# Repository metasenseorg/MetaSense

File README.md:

# MetaSense
MetaSense Project Repository of Data, Software, and Hardware.

Archival website: https://sites.google.com/a/eng.ucsd.edu/citisense/

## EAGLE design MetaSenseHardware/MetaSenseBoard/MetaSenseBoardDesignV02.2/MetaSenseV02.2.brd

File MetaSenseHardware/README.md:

# README #

[MetaSense Project](http://metasense.ucsd.edu)

# MetaSense Hardware #
This repository contains the hardware (electrical and mechanical enclosures) for the MetaSense Air Quality Sensing Platform.

## MetaSenseBoard ##
The electrical design for the MetaSense Air Quality Sensing Platform can be found here. A schematic can be found in each MetaSenseBoardDesign version folder along with gerbers that can be used for ordering and building PCBs.

If you want to modify or update the board files, the .brd and .sch files can be opened in Eagle.

### VOC Interface Board ###
The VOC interface board connects into the VOC and I2C Extension header (JP14). The board connects to two different VOC sensors:
* Mocon pID-TECH eVx: photoionization VOC sensor with 4-pin connection and analog output
* ams iAQ-core: MOS VOC sensor with I2C interface for TVOC equivalent measurement

## MetaSense Enclosure ##
The enclosures were developed in Autodesk Fusion. Both are meant to be used without the VOC interface board.

### Enclosure v1.3 ###
The standard enclosure for the MetaSense Air Quality Sensing Platform. The shell is split into top and bottom halves, which are connected by through bolts that both hold the board in place and secure the shell. Velcro straps can be run through the bottom to allow attachment to objects.

### Alternate Drone v1.3 ###
The alternate enclosure for the MetaSense Air Quality Sensing Platform allows the sensor to be connected directly to the bottom of a DJI F450 Quadcopter base.

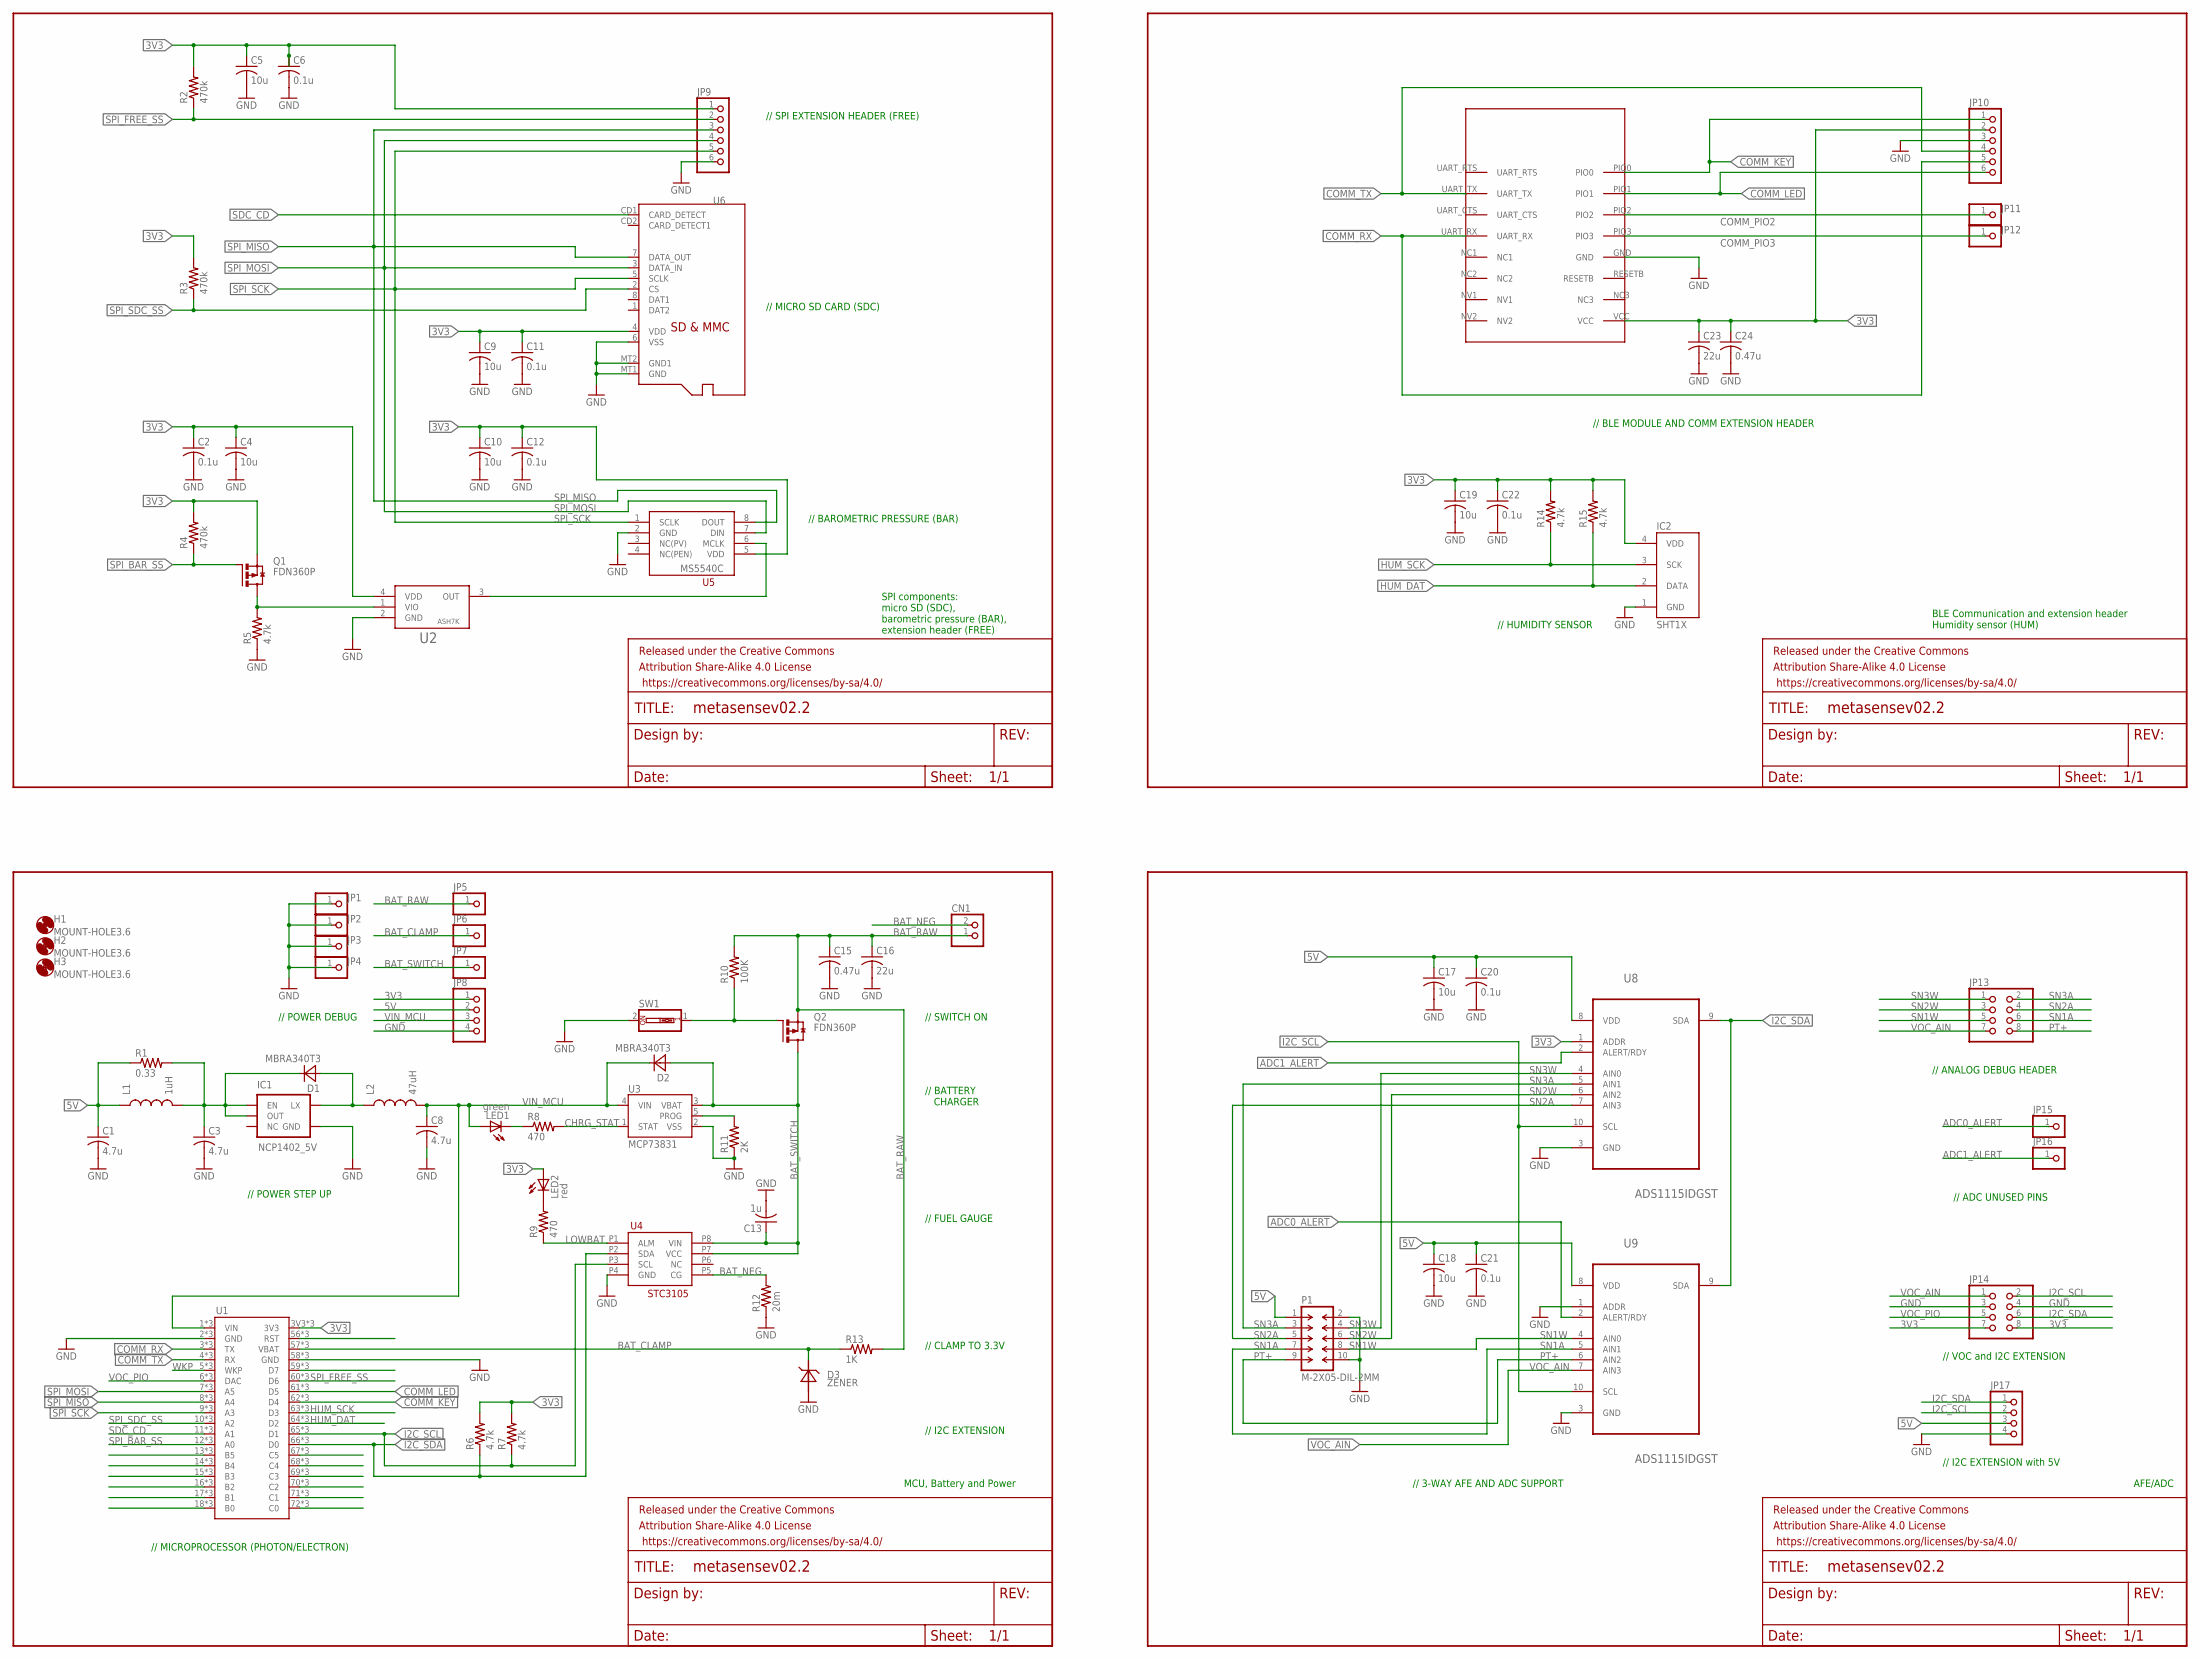
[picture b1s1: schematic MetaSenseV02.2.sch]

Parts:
C1, C3, C8: 4.7u; C0805; MPN IHLP2525CZER4R7M01
C2, C6, C11, C12, C20, C21, C22: 0.1u; C0805; MPN C0603C102J5GACTU
C4, C5, C9, C10, C17, C18, C19: 10u; C0805; MPN C0805C106Z8VACTU
C13: 1u; C0805; MPN C0402C471K5RACTU
C15, C24: 0.47u; C0805; MPN C0402C471K5RACTU
C16, C23: 22u; C0805
CN1: JST_2PIN-THM; JST-PH-2-THM
D1, D2: MBRA340T3; SMA
D3: ZENER; SOD-123_MINI-SMA
FRAME1, FRAME2, FRAME3, FRAME4: FRAME-LETTERNO_PACKAGE; DUMMY
H1, H2, H3: MOUNT-HOLE3.6; 3,6
IC1: NCP1402_5V; SOT23-5; MPN NCP1402SN50T1G
IC2: SHT1X; MPN SHT11
JP1, JP2, JP3, JP4, JP5, JP6, JP7, JP11, JP12, JP15, JP16: PINHD-1X1; 1X01
JP8, JP17: PINHD-1X4; 1X04
JP9, JP10: PINHD-1X6; 1X06
JP13, JP14: PINHD-2X4; 2X04
L1: 1uH; 0805; MPN LQM21NN1R0K10D
L2: 47uH; 0805
LED1: green; CHIPLED_0805; MPN NTE30003
LED2: red; CHIPLED_0805; MPN NTE30002
P1: M-2X05-DIL-2MM; DIL-2MM-2X05
Q1, Q2: FDN360P; SUPER-SOT3; MPN FDN360P
R1: 0.33; R0805
R2, R3, R4: 470k; R0805; MPN CRCW0805470KJNEA
R5, R6, R7, R14, R15: 4.7k; R0805; MPN CRCW08054K70JNEA
R8, R9: 470; R0805
R10: 100K; R0805; MPN ERA-6AEB104V
R11: 2K; R0805
R12: 20m; R0805
R13: 1K; R0805; MPN ERJ-6ENF1001V
SW1: SW_DIP-1; EDG-01
U1: ELECTRONDUALROW; ELECTRON_DUAL-ROW
U2: ASH7K-OSCILLATOR; SMD-4PAD
U3: MCP73831; SOT23-5; MPN MCP73831T-2DCI/OT
U4: STC3105; TDFN-8-3X2MM
U5: MS5540CSMD; SMD-HYBRID
U6: MICROSD; MPN 2908-05WB-MG
U7: HM-11
U8, U9: ADS1115IDGST; SOP50P490X110-10N

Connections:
3V3: C2.1, C4.1, C5.1, C6.1, C9.1, C10.1, C11.1, C12.1, C19.1, C22.1, C23.1, C24.1, IC2.4 (VDD), JP8.1, JP9.1, JP10.2, JP14.7, JP14.8, LED2.A, Q1.2 (S), R2.2, R3.2, R4.2, R6.2, R7.2, R14.2, R15.2, U1.3V3, U1.55 (3V3), U1.91 (3V3), U2.4 (VDD), U5.5 (VDD), U6.4 (VDD), U7.VCC, U8.1 (ADDR)
5V: C1.1, C17.1, C18.1, C20.1, C21.1, JP8.2, JP17.3, L1.1, P1.1, R1.1, U8.8 (VDD), U9.8 (VDD)
ADC0_ALERT: JP15.1, U9.2 (ALERT/RDY)
ADC1_ALERT: JP16.1, U8.2 (ALERT/RDY)
BAT_CLAMP: D3.C (CAT), JP6.1, R13.1, U1.57 (VBAT), U1.93 (VBAT), U1.VBAT
BAT_NEG: CN1.2 (1), R12.2, U4.P5 (CG)
BAT_RAW: C15.1, C16.1, CN1.1 (2), JP5.1, Q2.2 (S), R10.2, R13.2
BAT_SWITCH: C13.1, D2.A, JP7.1, Q2.3 (D), U3.3 (VBAT), U4.P7 (VCC), U4.P8 (VIN)
CHRG_STAT: R8.2, U3.1 (STAT)
COMM_KEY: JP10.1, U1.62 (D4), U1.98 (D4), U1.D4, U7.PIO0
COMM_LED: JP10.6, U1.61 (D5), U1.97 (D5), U1.D5, U7.PIO1
COMM_PIO2: JP11.1, U7.PIO2
COMM_PIO3: JP12.1, U7.PIO3
COMM_RX: JP10.5, U1.3 (TX), U1.39 (TX), U1.TX, U7.UART_RX
COMM_TX: JP10.4, U1.4 (RX), U1.40 (RX), U1.RX, U7.UART_TX
GND: C1.2, C2.2, C3.2, C4.2, C5.2, C6.2, C8.2, C9.2, C10.2, C11.2, C12.2, C13.2, C15.2, C16.2, C17.2, C18.2, C19.2, C20.2, C21.2, C22.2, C23.2, C24.2, D3.A (AN), IC1.4 (GND), IC2.1 (GND), JP1.1, JP2.1, JP3.1, JP4.1, JP8.4, JP9.6, JP10.3, JP14.3, JP14.4, JP17.4, P1.2, P1.10, R5.1, R11.1, R12.1, SW1.2, U1.2 (GND), U1.38 (GND), U1.58 (GND), U1.94 (GND), U1.GND, U1.GND@2 (GND), U2.2 (GND), U3.2 (VSS), U4.P4 (GND), U5.2 (GND), U6.6 (VSS), U6.MT1 (GND), U6.MT2 (GND1), U7.GND, U8.3 (GND), U9.1 (ADDR), U9.3 (GND)
HUM_DAT: IC2.2 (DATA), R15.1, U1.64 (D2), U1.100 (D2), U1.D2
HUM_SCK: IC2.3 (SCK), R14.1, U1.63 (D3), U1.99 (D3), U1.D3
I2C_SCL: JP14.2, JP17.2, R7.1, U1.65 (D1), U1.101 (D1), U1.D1, U4.P3 (SCL), U8.10 (SCL), U9.10 (SCL)
I2C_SDA: JP14.6, JP17.1, R6.1, U1.66 (D0), U1.102 (D0), U1.D0, U4.P2 (SDA), U8.9 (SDA), U9.9 (SDA)
LOWBAT: R9.1, U4.P1 (ALM)
unnamed: Q1.3 (D), R5.2, U2.1 (VIO)
unnamed: C3.1, D1.C, IC1.1 (EN), IC1.2 (OUT), L1.2, R1.2
unnamed: LED2.C, R9.2
unnamed: D1.A, IC1.5 (LX), L2.1
unnamed: U1.56 (RST), U1.92 (RST), U1.RST
unnamed: U1.67 (C5), U1.103 (C5), U1.C5
unnamed: R11.2, U3.5 (PROG)
unnamed: LED1.C, R8.1
unnamed: Q2.1 (G), R10.1, SW1.1
unnamed: U1.68 (C4), U1.104 (C4), U1.C4
unnamed: U2.3 (OUT), U5.6 (MCLK)
unnamed: U1.69 (C3), U1.105 (C3), U1.C3
unnamed: U1.70 (C2), U1.106 (C2), U1.C2
unnamed: U1.71 (C1), U1.107 (C1), U1.C1
unnamed: U1.72 (C0), U1.108 (C0), U1.C0
unnamed: U1.13 (B5), U1.49 (B5), U1.B5
unnamed: U1.59 (D7), U1.95 (D7), U1.D7
unnamed: U1.14 (B4), U1.50 (B4), U1.B4
unnamed: U1.15 (B3), U1.51 (B3), U1.B3
unnamed: U1.16 (B2), U1.52 (B2), U1.B2
unnamed: U1.17 (B1), U1.53 (B1), U1.B1
unnamed: U1.18 (B0), U1.54 (B0), U1.B0
PT+: JP13.8, P1.9, U9.6 (AIN2)
SDC_CD: U1.11 (A1), U1.47 (A1), U1.A1, U6.CD1 (CARD_DETECT)
SN1A: JP13.6, P1.7, U9.5 (AIN1)
SN1W: JP13.5, P1.8, U9.4 (AIN0)
SN2A: JP13.4, P1.5, U8.7 (AIN3)
SN2W: JP13.3, P1.6, U8.6 (AIN2)
SN3A: JP13.2, P1.3, U8.5 (AIN1)
SN3W: JP13.1, P1.4, U8.4 (AIN0)
SPI_BAR_SS: Q1.1 (G), R4.1, U1.12 (A0), U1.48 (A0), U1.A0
SPI_FREE_SS: JP9.2, R2.1, U1.60 (D6), U1.96 (D6), U1.D6
SPI_MISO: JP9.3, U1.8 (A4), U1.44 (A4), U1.A4, U5.8 (DOUT), U6.7 (DATA_OUT)
SPI_MOSI: JP9.4, U1.7 (A5), U1.43 (A5), U1.A5, U5.7 (DIN), U6.3 (DATA_IN)
SPI_SCK: JP9.5, U1.9 (A3), U1.45 (A3), U1.A3, U5.1 (SCLK), U6.5 (SCLK)
SPI_SDC_SS: R3.1, U1.10 (A2), U1.46 (A2), U1.A2, U6.2 (CS)
VIN_MCU: C8.1, D2.C, JP8.3, L2.2, LED1.A, U1.1 (VIN), U1.37 (VIN), U1.VIN, U3.4 (VIN)
VOC_AIN: JP13.7, JP14.1, U9.7 (AIN3)
VOC_PIO: JP14.5, U1.6 (DAC), U1.42 (DAC), U1.DAC
WKP: U1.5 (WKP), U1.41 (WKP), U1.WKP

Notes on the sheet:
MCU, Battery and Power
AFE/ADC
SPI components: micro SD (SDC), barometric pressure (BAR), extension header (FREE)
// BATTERY CHARGER
// FUEL GAUGE
// SWITCH ON
// POWER STEP UP
// 3-WAY AFE AND ADC SUPPORT
// BLE MODULE AND COMM EXTENSION HEADER
// HUMIDITY SENSOR
// SPI EXTENSION HEADER (FREE)
// MICRO SD CARD (SDC)
// BAROMETRIC PRESSURE (BAR)
BLE Communication and extension header Humidity sensor (HUM)
// ANALOG DEBUG HEADER
// MICROPROCESSOR (PHOTON/ELECTRON)
// I2C EXTENSION
// POWER DEBUG
// CLAMP TO 3.3V
// ADC UNUSED PINS
// VOC and I2C EXTENSION
// I2C EXTENSION with 5V

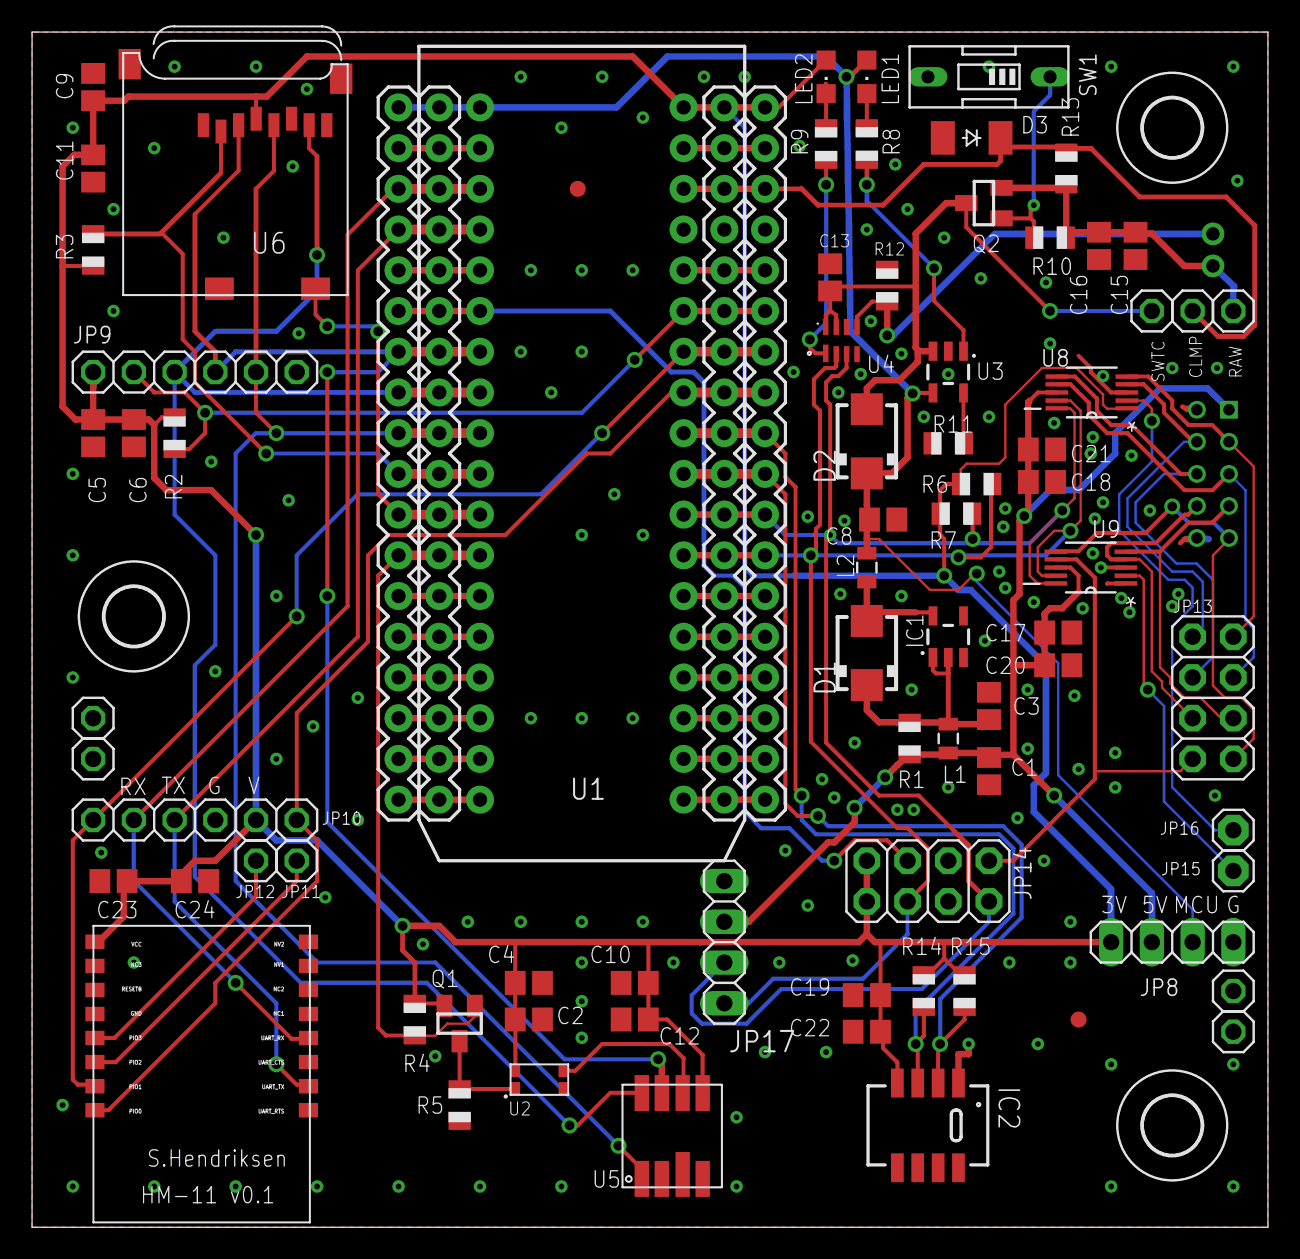
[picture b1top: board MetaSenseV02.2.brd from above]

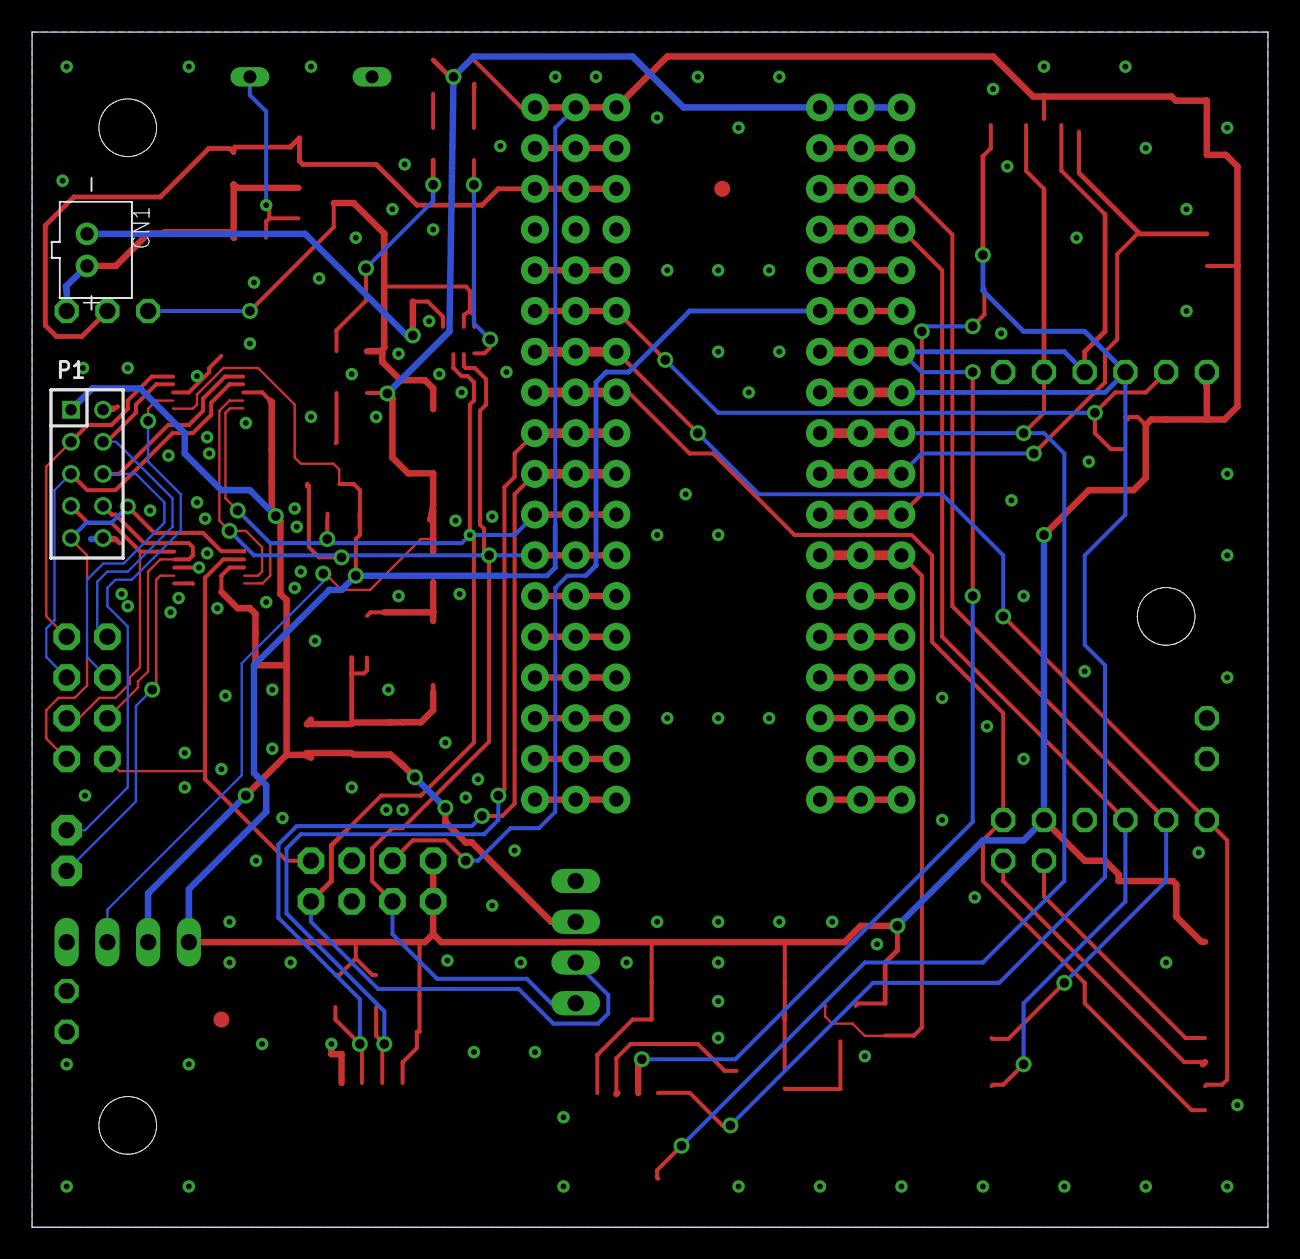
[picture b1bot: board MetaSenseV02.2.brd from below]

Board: 2 copper layers, 77.1 x 74.5 mm, 84 parts (2 on the bottom side), 61 nets.

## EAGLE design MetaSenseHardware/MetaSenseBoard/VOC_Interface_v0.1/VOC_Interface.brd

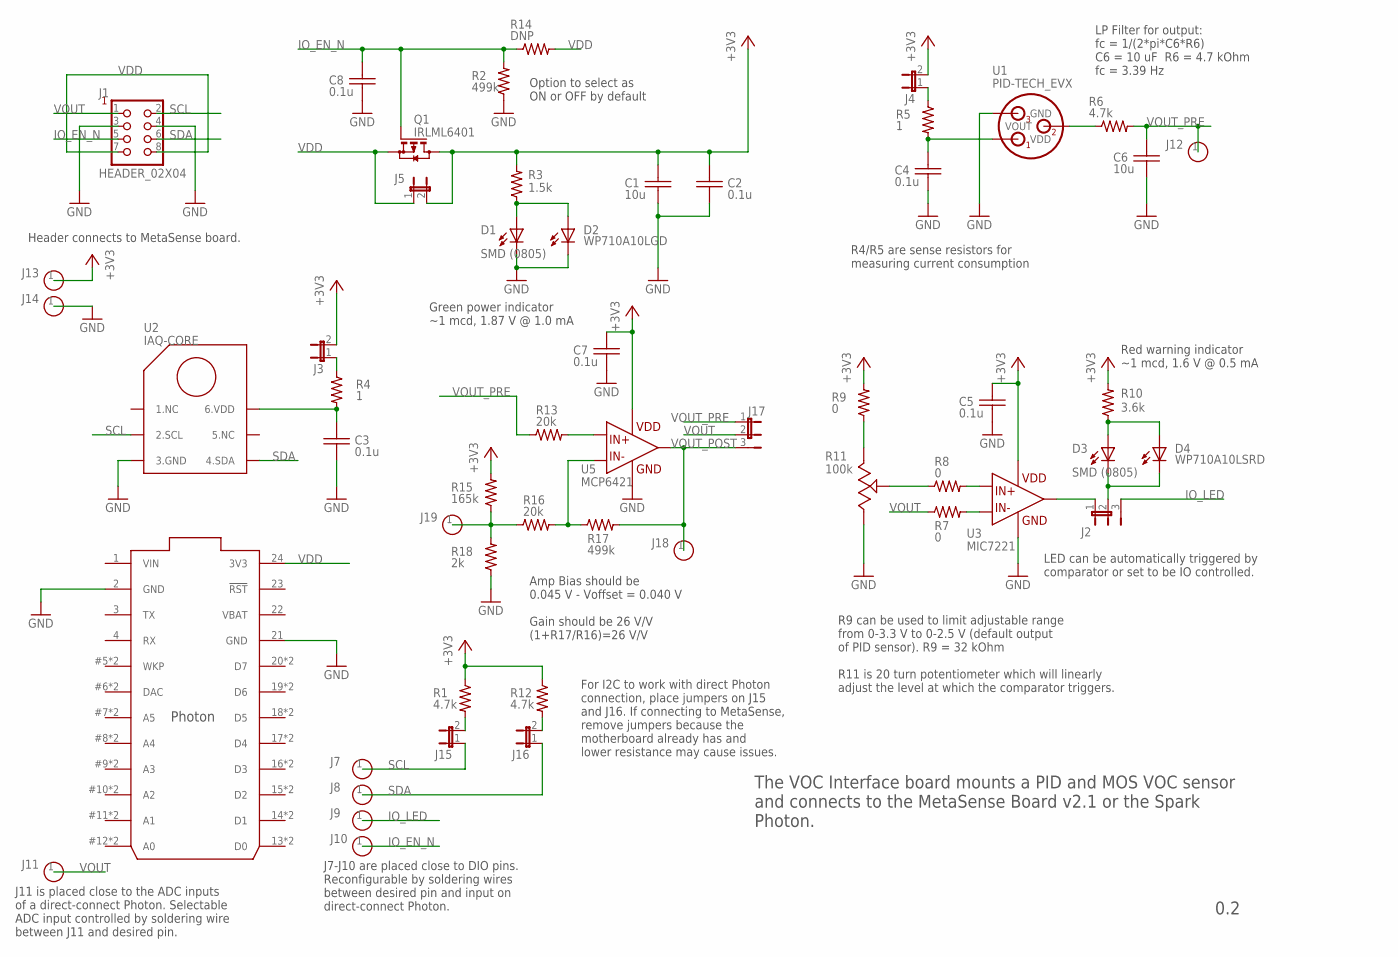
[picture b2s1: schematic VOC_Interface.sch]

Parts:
C1, C6: 10u; C0805
C2, C3, C4, C5, C7, C8: 0.1u; C0805
D1, D3: SMD (0805); CHIPLED_0805
D2: WP710A10LGD; LED3MM
D4: WP710A10LSRD; LED3MM
J1: HEADER_02X04; 2X04
J2, J17: HEADER_01X03; 1X03
J3, J4, J5, J15, J16: HEADER_01X02; 1X02
J7, J8, J9, J10, J11, J12, J13, J14, J18, J19: HEADER_01X01; 1X01
Q1: IRLML6401; SOT23
R1, R6, R12: 4.7k; R0805
R2, R17: 499k; R0805
R3: 1.5k; R0805
R4, R5: 1; R0805
R7, R8, R9: 0; R0805
R10: 3.6k; R0805
R11: 100k; POTTRIM_TOP
R13, R16: 20k; R0805
R14: DNP; R0805
R15: 165k; R0805
R18: 2k; R0805
U1: PID-TECH_EVX; VOC_PID_3SOCKET
U2: IAQ-CORE
U3: MIC7221; SOT-23-5
U4: PHOTON; PHOTON_STACKABLE
U5: MCP6421; SOT-23-5

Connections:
+3V3: C1.2, C2.2, C5.2, C7.2, J3.2, J4.2, J5.2, J13.1, Q1.3 (D), R1.1, R3.2, R9.2, R10.2, R12.1, R15.2, U3.2 (2.VDD), U5.5 (2.VDD)
AMP_IN+: R13.2, U5.3 (3.IN+)
AMP_IN-: R16.2, R17.1, U5.4 (4.IN-)
AMP_VBIAS: J19.1, R15.1, R16.1, R18.2
GND: C1.1, C2.1, C3.1, C4.1, C5.1, C6.1, C7.1, C8.1, D1.C, D2.C, J1.3, J1.4, J14.1, R2.1, R11.3, R18.1, U1.3_GND (GND), U2.3 (3.GND), U3.5 (5.GND), U4.2 (GND), U4.21 (GND), U5.2 (5.GND)
IO_EN_N: C8.2, J1.5, J10.1, Q1.1 (G), R2.2, R14.1
IO_LED: J2.3, J9.1
unnamed: J2.1, U3.1 (1.VOUT)
unnamed: D3.C, D4.C, J2.2
unnamed: D1.A, D2.A, R3.1
unnamed: D3.A, D4.A, R10.1
unnamed: R9.1, R11.1
unnamed: R8.1, R11.2
unnamed: J3.1, R4.1
unnamed: J4.1, R5.1
unnamed: J16.2, R12.2
unnamed: J15.2, R1.2
unnamed: R8.2, U3.3 (3.IN+)
unnamed: R7.2, U3.4 (4.IN-)
SCL: J1.2, J7.1, J15.1, U2.2 (2.SCL)
SDA: J1.6, J8.1, J16.1, U2.4 (4.SDA)
VBAT: U4.22 (VBAT)
VDD: J1.7, J1.8, J5.1, Q1.2 (S), R14.2, U4.24 (3V3)
VDD_MOS: C3.2, R4.2, U2.6 (6.VDD)
VDD_PID: C4.2, R5.2, U1.1_VDD (VDD)
VIN: U4.1 (VIN)
VOUT: J1.1, J11.1, J17.2, R7.1
VOUT_POST: J17.3, J18.1, R17.2, U5.1 (1.VOUT)
VOUT_PRE: C6.2, J12.1, J17.1, R6.2, R13.1
VVOC: R6.1, U1.2_VOUT (VOUT)

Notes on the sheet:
Option to select as ON or OFF by default
LP Filter for output: fc = 1/(2*pi*C6*R6) C6 = 10 uF R6 = 4.7 kOhm fc = 3.39 Hz
R9 can be used to limit adjustable range from 0-3.3 V to 0-2.5 V (default output of PID sensor). R9 = 32 kOhm R11 is 20 turn potentiometer which will linearly adjust the level at which the comparator triggers.
LED can be automatically triggered by comparator or set to be IO controlled.
For I2C to work with direct Photon connection, place jumpers on J15 and J16. If connecting to MetaSense, remove jumpers because the motherboard already has and lower resistance may cause issues.
J11 is placed close to the ADC inputs of a direct-connect Photon. Selectable ADC input controlled by soldering wire between J11 and desired pin.
J7-J10 are placed close to DIO pins. Reconfigurable by soldering wires between desired pin and input on direct-connect Photon.
Header connects to MetaSense board.
Green power indicator ~1 mcd, 1.87 V @ 1.0 mA
Red warning indicator ~1 mcd, 1.6 V @ 0.5 mA
R4/R5 are sense resistors for measuring current consumption
Amp Bias should be 0.045 V - Voffset = 0.040 V Gain should be 26 V/V (1+R17/R16)=26 V/V
0.2
The VOC Interface board mounts a PID and MOS VOC sensor and connects to the MetaSense Board v2.1 or the Spark Photon.

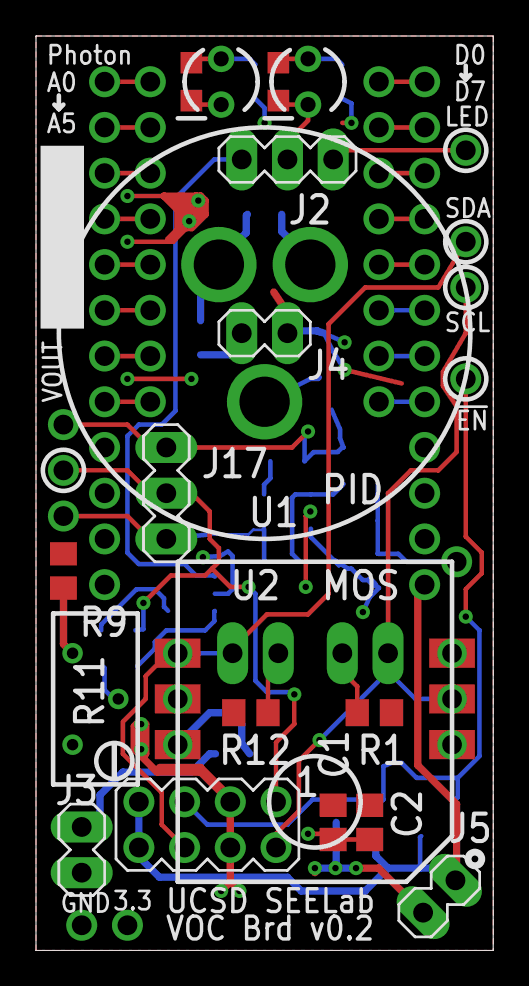
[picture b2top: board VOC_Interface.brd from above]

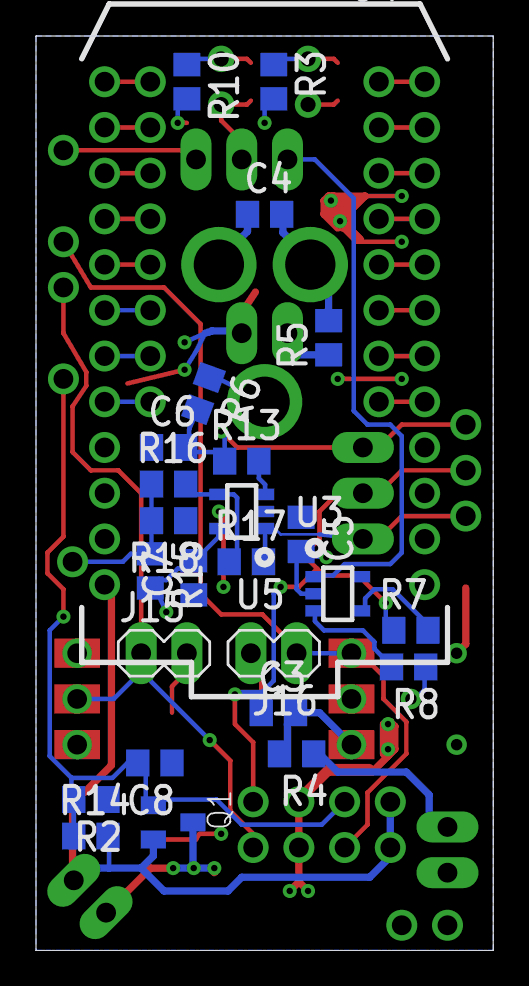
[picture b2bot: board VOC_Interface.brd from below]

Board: 2 copper layers, 25.4 x 50.8 mm, 54 parts (26 on the bottom side), 28 nets.

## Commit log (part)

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2019-05-08 First Publication of Open Source software and data for the MetaSense Project
2019-10-31 Bump werkzeug from 0.14.1 to 0.15.3 in /MetaSenseTransfer
    Bumps [werkzeug](https://github.com/pallets/werkzeug) from 0.14.1 to 0.15.3.
    - [Release notes](https://github.com/pallets/werkzeug/releases)
    - [Changelog](https://github.com/pallets/werkzeug/blob/master/CHANGES.rst)
    - [Commits](https://github.com/pallets/werkzeug/compare/0.14.1...0.15.3)
2019-11-08 Bump notebook from 5.4.1 to 5.7.8 in /MetaSenseTransfer
    Bumps [notebook](https://github.com/jupyter/jupyterhub) from 5.4.1 to 5.7.8.
    - [Release notes](https://github.com/jupyter/jupyterhub/releases)
    - [Changelog](https://github.com/jupyterhub/jupyterhub/blob/master/CHECKLIST-Release.md)
    - [Commits](https://github.com/jupyter/jupyterhub/commits)
2019-12-16 Bump tensorflow from 1.7.0 to 1.15.0 in /MetaSenseTransfer
    Bumps [tensorflow](https://github.com/tensorflow/tensorflow) from 1.7.0 to 1.15.0.
    - [Release notes](https://github.com/tensorflow/tensorflow/releases)
    - [Changelog](https://github.com/tensorflow/tensorflow/blob/master/RELEASE.md)
    - [Commits](https://github.com/tensorflow/tensorflow/compare/v1.7.0...v1.15.0)
2020-01-28 Bump tensorflow from 1.7.0 to 1.15.2 in /MetaSenseTransfer
    Bumps [tensorflow](https://github.com/tensorflow/tensorflow) from 1.7.0 to 1.15.2.
    - [Release notes](https://github.com/tensorflow/tensorflow/releases)
    - [Changelog](https://github.com/tensorflow/tensorflow/blob/master/RELEASE.md)
    - [Commits](https://github.com/tensorflow/tensorflow/compare/v1.7.0...v1.15.2)
2020-03-24 Bump bleach from 1.5.0 to 3.1.2 in /MetaSenseTransfer
    Bumps [bleach](https://github.com/mozilla/bleach) from 1.5.0 to 3.1.2.
    - [Release notes](https://github.com/mozilla/bleach/releases)
    - [Changelog](https://github.com/mozilla/bleach/blob/master/CHANGES)
    - [Commits](https://github.com/mozilla/bleach/compare/v1.5...v3.1.2)
2020-03-31 Bump bleach from 1.5.0 to 3.1.4 in /MetaSenseTransfer
    Bumps [bleach](https://github.com/mozilla/bleach) from 1.5.0 to 3.1.4.
    - [Release notes](https://github.com/mozilla/bleach/releases)
    - [Changelog](https://github.com/mozilla/bleach/blob/master/CHANGES)
    - [Commits](https://github.com/mozilla/bleach/compare/v1.5...v3.1.4)
2020-04-16 Added MetaSenseHardware to repository
2020-09-25 Bump tensorflow from 1.7.0 to 1.15.4 in /MetaSenseTransfer
    Bumps [tensorflow](https://github.com/tensorflow/tensorflow) from 1.7.0 to 1.15.4.
    - [Release notes](https://github.com/tensorflow/tensorflow/releases)
    - [Changelog](https://github.com/tensorflow/tensorflow/blob/master/RELEASE.md)
    - [Commits](https://github.com/tensorflow/tensorflow/compare/v1.7.0...v1.15.4)
2020-11-18 Bump notebook from 5.4.1 to 6.1.5 in /MetaSenseTransfer
    Bumps [notebook](https://github.com/jupyter/jupyterhub) from 5.4.1 to 6.1.5.
    - [Release notes](https://github.com/jupyter/jupyterhub/releases)
    - [Changelog](https://github.com/jupyterhub/jupyterhub/blob/master/CHECKLIST-Release.md)
    - [Commits](https://github.com/jupyter/jupyterhub/commits)
2021-02-02 Bump bleach from 1.5.0 to 3.3.0 in /MetaSenseTransfer
    Bumps [bleach](https://github.com/mozilla/bleach) from 1.5.0 to 3.3.0.
    - [Release notes](https://github.com/mozilla/bleach/releases)
    - [Changelog](https://github.com/mozilla/bleach/blob/master/CHANGES)
    - [Commits](https://github.com/mozilla/bleach/compare/v1.5...v3.3.0)
2021-03-20 Bump jinja2 from 2.10 to 2.11.3 in /MetaSenseTransfer
    Bumps [jinja2](https://github.com/pallets/jinja) from 2.10 to 2.11.3.
    - [Release notes](https://github.com/pallets/jinja/releases)
    - [Changelog](https://github.com/pallets/jinja/blob/master/CHANGES.rst)
    - [Commits](https://github.com/pallets/jinja/compare/2.10...2.11.3)
2021-03-29 Bump pygments from 2.2.0 to 2.7.4 in /MetaSenseTransfer
    Bumps [pygments](https://github.com/pygments/pygments) from 2.2.0 to 2.7.4.
    - [Release notes](https://github.com/pygments/pygments/releases)
    - [Changelog](https://github.com/pygments/pygments/blob/master/CHANGES)
    - [Commits](https://github.com/pygments/pygments/compare/2.2.0...2.7.4)
2021-08-04 Bump System.Text.RegularExpressions in /MetaSenseApps/Receiver.Form
    Bumps System.Text.RegularExpressions from 4.3.0 to 4.3.1.
    ---
    updated-dependencies:
    - dependency-name: System.Text.RegularExpressions
    dependency-type: direct:production
    ...
2021-08-04 Bump System.Text.RegularExpressions in /MetaSenseApps/Configurator.iOS
    Bumps System.Text.RegularExpressions from 4.3.0 to 4.3.1.
    ---
    updated-dependencies:
    - dependency-name: System.Text.RegularExpressions
    dependency-type: direct:production
    ...
2021-08-04 Bump System.Text.RegularExpressions in /MetaSenseApps/Core.NodeLibrary
    Bumps System.Text.RegularExpressions from 4.3.0 to 4.3.1.
    ---
    updated-dependencies:
    - dependency-name: System.Text.RegularExpressions
    dependency-type: direct:production
    ...
2021-08-04 Bump System.Text.RegularExpressions in /MetaSenseApps/Core.Droid
    Bumps System.Text.RegularExpressions from 4.3.0 to 4.3.1.
    ---
    updated-dependencies:
    - dependency-name: System.Text.RegularExpressions
    dependency-type: direct:production
    ...
2021-08-04 Bump System.Text.RegularExpressions in /MetaSenseApps/Receiver.Droid
    Bumps System.Text.RegularExpressions from 4.3.0 to 4.3.1.
    ---
    updated-dependencies:
    - dependency-name: System.Text.RegularExpressions
    dependency-type: direct:production
    ...
2021-08-04 Bump System.Text.RegularExpressions
    Bumps System.Text.RegularExpressions from 4.3.0 to 4.3.1.
    ---
    updated-dependencies:
    - dependency-name: System.Text.RegularExpressions
    dependency-type: direct:production
    ...
2021-08-04 Bump System.Text.RegularExpressions in /MetaSenseApps/Configurator.Form
    Bumps System.Text.RegularExpressions from 4.3.0 to 4.3.1.
    ---
    updated-dependencies:
    - dependency-name: System.Text.RegularExpressions
    dependency-type: direct:production
    ...
2021-08-25 Bump tensorflow from 1.7.0 to 2.5.1 in /MetaSenseTransfer
    Bumps [tensorflow](https://github.com/tensorflow/tensorflow) from 1.7.0 to 2.5.1.
    - [Release notes](https://github.com/tensorflow/tensorflow/releases)
    - [Changelog](https://github.com/tensorflow/tensorflow/blob/master/RELEASE.md)
    - [Commits](https://github.com/tensorflow/tensorflow/compare/v1.7.0...v2.5.1)
    ---
    updated-dependencies:
2022-02-10 Bump tensorflow from 1.7.0 to 2.5.3 in /MetaSenseTransfer
    Bumps [tensorflow](https://github.com/tensorflow/tensorflow) from 1.7.0 to 2.5.3.
    - [Release notes](https://github.com/tensorflow/tensorflow/releases)
    - [Changelog](https://github.com/tensorflow/tensorflow/blob/master/RELEASE.md)
    - [Commits](https://github.com/tensorflow/tensorflow/compare/v1.7.0...v2.5.3)
    ---
    updated-dependencies:
2022-02-11 Bump protobuf from 3.5.2.post1 to 3.15.0 in /MetaSenseTransfer
    Bumps [protobuf](https://github.com/protocolbuffers/protobuf) from 3.5.2.post1 to 3.15.0.
    - [Release notes](https://github.com/protocolbuffers/protobuf/releases)
    - [Changelog](https://github.com/protocolbuffers/protobuf/blob/master/generate_changelog.py)
    - [Commits](https://github.com/protocolbuffers/protobuf/commits/v3.15.0)
    ---
    updated-dependencies:
2022-04-06 Bump notebook from 5.4.1 to 6.4.10 in /MetaSenseTransfer
    Bumps [notebook](http://jupyter.org) from 5.4.1 to 6.4.10.
    ---
    updated-dependencies:
    - dependency-name: notebook
    dependency-type: direct:production
    ...
2022-05-24 Bump tensorflow from 1.7.0 to 2.6.4 in /MetaSenseTransfer
    Bumps [tensorflow](https://github.com/tensorflow/tensorflow) from 1.7.0 to 2.6.4.
    - [Release notes](https://github.com/tensorflow/tensorflow/releases)
    - [Changelog](https://github.com/tensorflow/tensorflow/blob/master/RELEASE.md)
    - [Commits](https://github.com/tensorflow/tensorflow/compare/v1.7.0...v2.6.4)
    ---
    updated-dependencies:
2022-06-02 Bump html5lib from 0.9999999 to 0.99999999 in /MetaSenseTransfer
    Bumps [html5lib](https://github.com/html5lib/html5lib-python) from 0.9999999 to 0.99999999.
    - [Release notes](https://github.com/html5lib/html5lib-python/releases)
    - [Changelog](https://github.com/html5lib/html5lib-python/blob/master/CHANGES.rst)
    - [Commits](https://github.com/html5lib/html5lib-python/compare/0.9999999...0.99999999)
    ---
    updated-dependencies:
2022-06-16 Bump notebook from 5.4.1 to 6.4.12 in /MetaSenseTransfer
    Bumps [notebook](http://jupyter.org) from 5.4.1 to 6.4.12.
    ---
    updated-dependencies:
    - dependency-name: notebook
    dependency-type: direct:production
    ...
2022-06-21 Bump numpy from 1.14.2 to 1.22.0 in /MetaSenseTransfer
    Bumps [numpy](https://github.com/numpy/numpy) from 1.14.2 to 1.22.0.
    - [Release notes](https://github.com/numpy/numpy/releases)
    - [Changelog](https://github.com/numpy/numpy/blob/main/doc/HOWTO_RELEASE.rst)
    - [Commits](https://github.com/numpy/numpy/compare/v1.14.2...v1.22.0)
    ---
    updated-dependencies:
2022-06-22 Bump Newtonsoft.Json in /MetaSenseApps/Core.NodeLibrary
    Bumps [Newtonsoft.Json](https://github.com/JamesNK/Newtonsoft.Json) from 12.0.2 to 13.0.1.
    - [Release notes](https://github.com/JamesNK/Newtonsoft.Json/releases)
    - [Commits](https://github.com/JamesNK/Newtonsoft.Json/compare/12.0.2...13.0.1)
    ---
    updated-dependencies:
    - dependency-name: Newtonsoft.Json
2022-07-29 Bump mistune from 0.8.3 to 2.0.3 in /MetaSenseTransfer
    Bumps [mistune](https://github.com/lepture/mistune) from 0.8.3 to 2.0.3.
    - [Release notes](https://github.com/lepture/mistune/releases)
    - [Changelog](https://github.com/lepture/mistune/blob/master/docs/changes.rst)
    - [Commits](https://github.com/lepture/mistune/compare/v0.8.3...v2.0.3)
    ---
    updated-dependencies:
2022-08-10 Bump nbconvert from 5.3.1 to 6.3.0 in /MetaSenseTransfer
    Bumps [nbconvert](https://github.com/jupyter/nbconvert) from 5.3.1 to 6.3.0.
    - [Release notes](https://github.com/jupyter/nbconvert/releases)
    - [Commits](https://github.com/jupyter/nbconvert/compare/5.3.1...6.3.0)
    ---
    updated-dependencies:
    - dependency-name: nbconvert
2022-08-23 Bump nbconvert from 5.3.1 to 6.5.1 in /MetaSenseTransfer
    Bumps [nbconvert](https://github.com/jupyter/nbconvert) from 5.3.1 to 6.5.1.
    - [Release notes](https://github.com/jupyter/nbconvert/releases)
    - [Commits](https://github.com/jupyter/nbconvert/compare/5.3.1...6.5.1)
    ---
    updated-dependencies:
    - dependency-name: nbconvert
2022-09-23 Bump protobuf from 3.5.2.post1 to 3.18.3 in /MetaSenseTransfer
    Bumps [protobuf](https://github.com/protocolbuffers/protobuf) from 3.5.2.post1 to 3.18.3.
    - [Release notes](https://github.com/protocolbuffers/protobuf/releases)
    - [Changelog](https://github.com/protocolbuffers/protobuf/blob/main/generate_changelog.py)
    - [Commits](https://github.com/protocolbuffers/protobuf/commits/v3.18.3)
    ---
    updated-dependencies:
2022-11-21 Bump tensorflow from 1.7.0 to 2.9.3 in /MetaSenseTransfer
    Bumps [tensorflow](https://github.com/tensorflow/tensorflow) from 1.7.0 to 2.9.3.
    - [Release notes](https://github.com/tensorflow/tensorflow/releases)
    - [Changelog](https://github.com/tensorflow/tensorflow/blob/master/RELEASE.md)
    - [Commits](https://github.com/tensorflow/tensorflow/compare/v1.7.0...v2.9.3)
    ---
    updated-dependencies:

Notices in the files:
parts and their libraries:
SparkFun-Passives: Licensing: Creative Commons ShareAlike 4.0 International - https://creativecommons.org/licenses/by-sa/4.0
con-headers-jp: Copyright (C) 2008, Bob Starr
SparkFun-Aesthetics: Released under the Creative Commons Attribution Share-Alike 4.0 License
